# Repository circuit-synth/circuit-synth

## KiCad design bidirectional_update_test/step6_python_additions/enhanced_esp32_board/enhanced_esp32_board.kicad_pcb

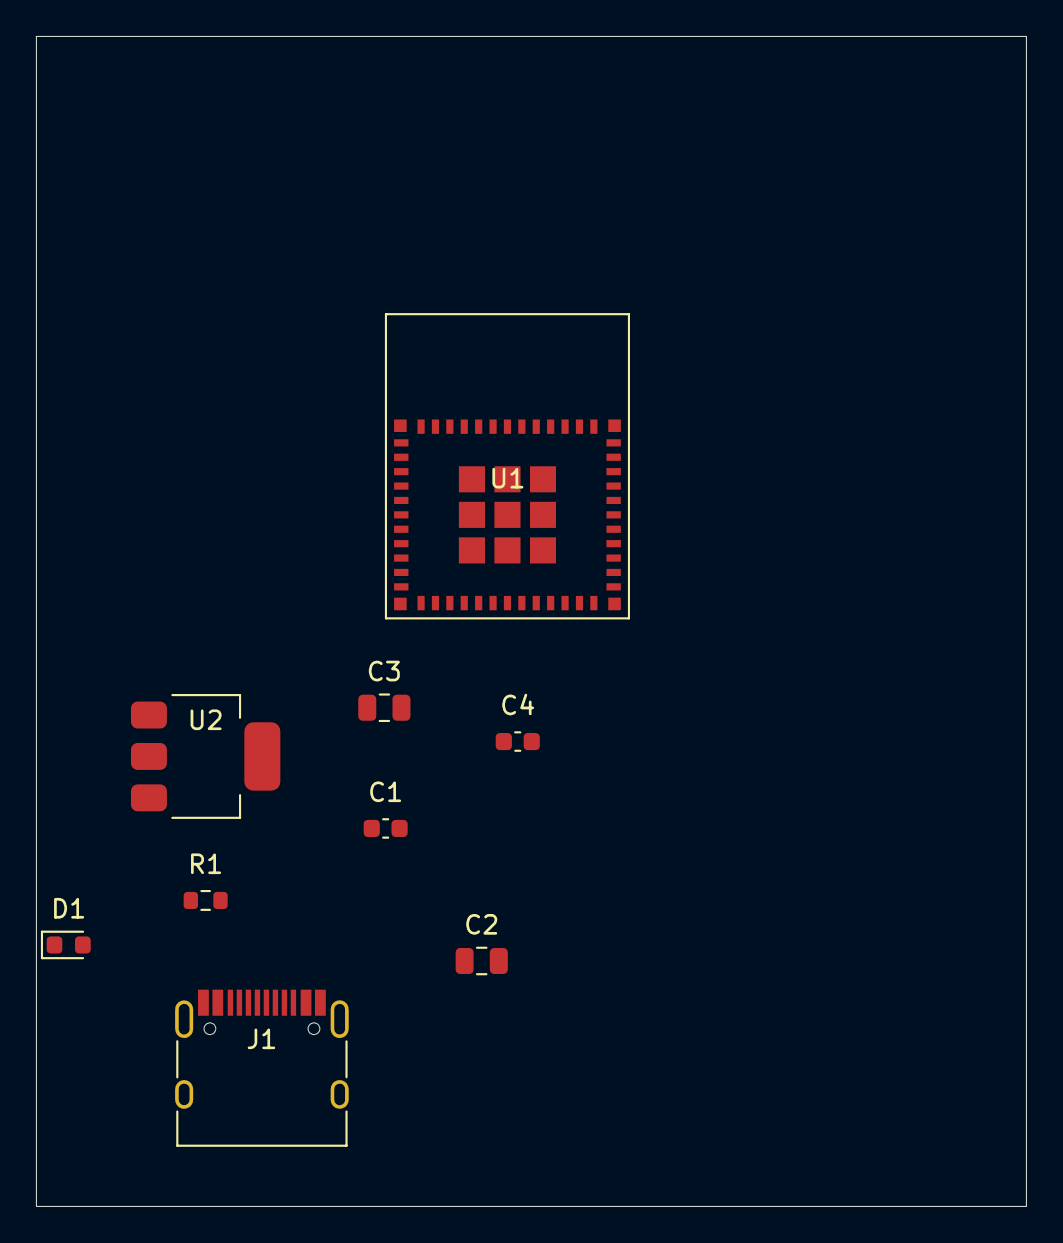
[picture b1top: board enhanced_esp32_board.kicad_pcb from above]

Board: 2 copper layers, 55.0 x 65.0 mm, 9 parts (0 on the bottom side), 4 nets, no tracks yet.

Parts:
C1: C; C_0603_1608Metric
C2: 10uF; C_0805_2012Metric
C3: 22uF; C_0805_2012Metric
C4: 100nF; C_0603_1608Metric
D1: Green LED; LED_0603_1608Metric
J1: USB-C; USB_C_Receptacle_HRO_TYPE-C-31-M-12
R1: 330R; R_0603_1608Metric
U1: ESP32-C6-MINI-1
U2: AMS1117-3.3; SOT-223-3_TabPin2

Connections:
+3V3: C1.1, C3.1, C4.1, R1.1, U1.3, U2.2
GND: C1.2, C2.2, C3.2, C4.2, D1.1, J1.A1, J1.A12, J1.B1, J1.B12, U1.1, U1.2, U1.11, U1.14, U1.36, U1.37, U1.38, U1.39, U1.40, U1.41, U1.42, U1.43, U1.44, U1.45, U1.46, U1.47, U1.48, U1.49, U1.50, U1.51, U1.52, U1.53, U2.1
LED_ANODE: D1.2, R1.2
VBUS_5V: C2.1, J1.A4, J1.A9, J1.B4, J1.B9, U2.3

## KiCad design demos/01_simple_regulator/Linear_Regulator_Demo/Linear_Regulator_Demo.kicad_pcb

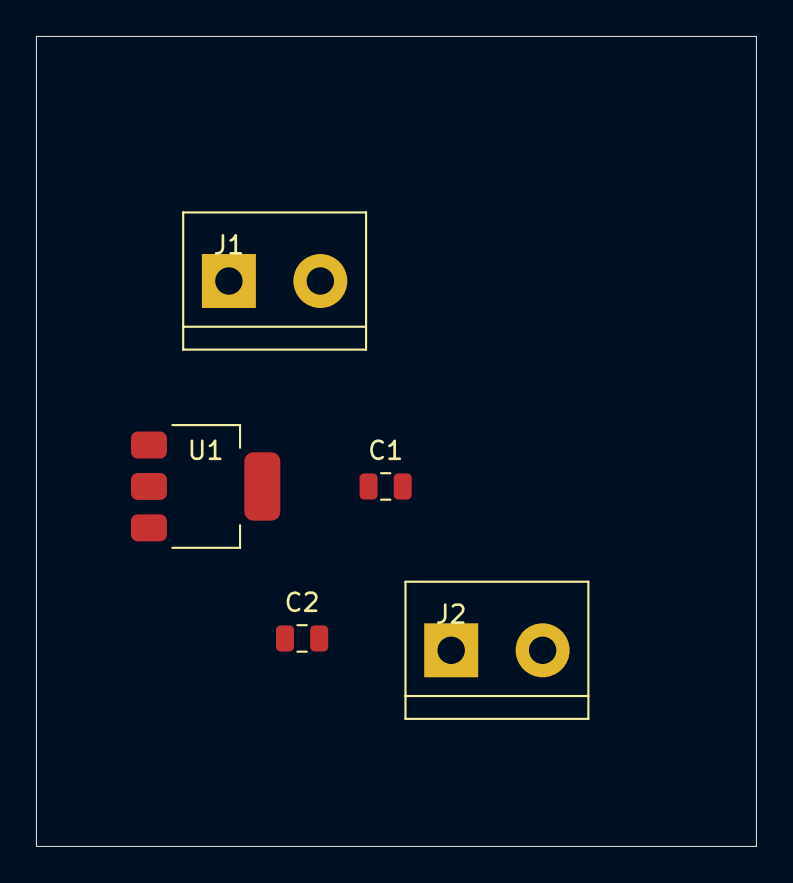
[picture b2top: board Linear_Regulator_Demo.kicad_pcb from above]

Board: 2 copper layers, 40.0 x 45.0 mm, 5 parts (0 on the bottom side), 3 nets, no tracks yet.

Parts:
C1: 10uF; C_0805_2012Metric
C2: 22uF; C_0805_2012Metric
J1, J2: TerminalBlock_bornier-2_P5.08mm
U1: SOT-223-3_TabPin2

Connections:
GND: C1.2, C2.2, J1.2, J2.2, U1.1
VIN_5V: C1.1, J1.1, U1.3
VOUT_3V3: C2.1, J2.1, U1.2

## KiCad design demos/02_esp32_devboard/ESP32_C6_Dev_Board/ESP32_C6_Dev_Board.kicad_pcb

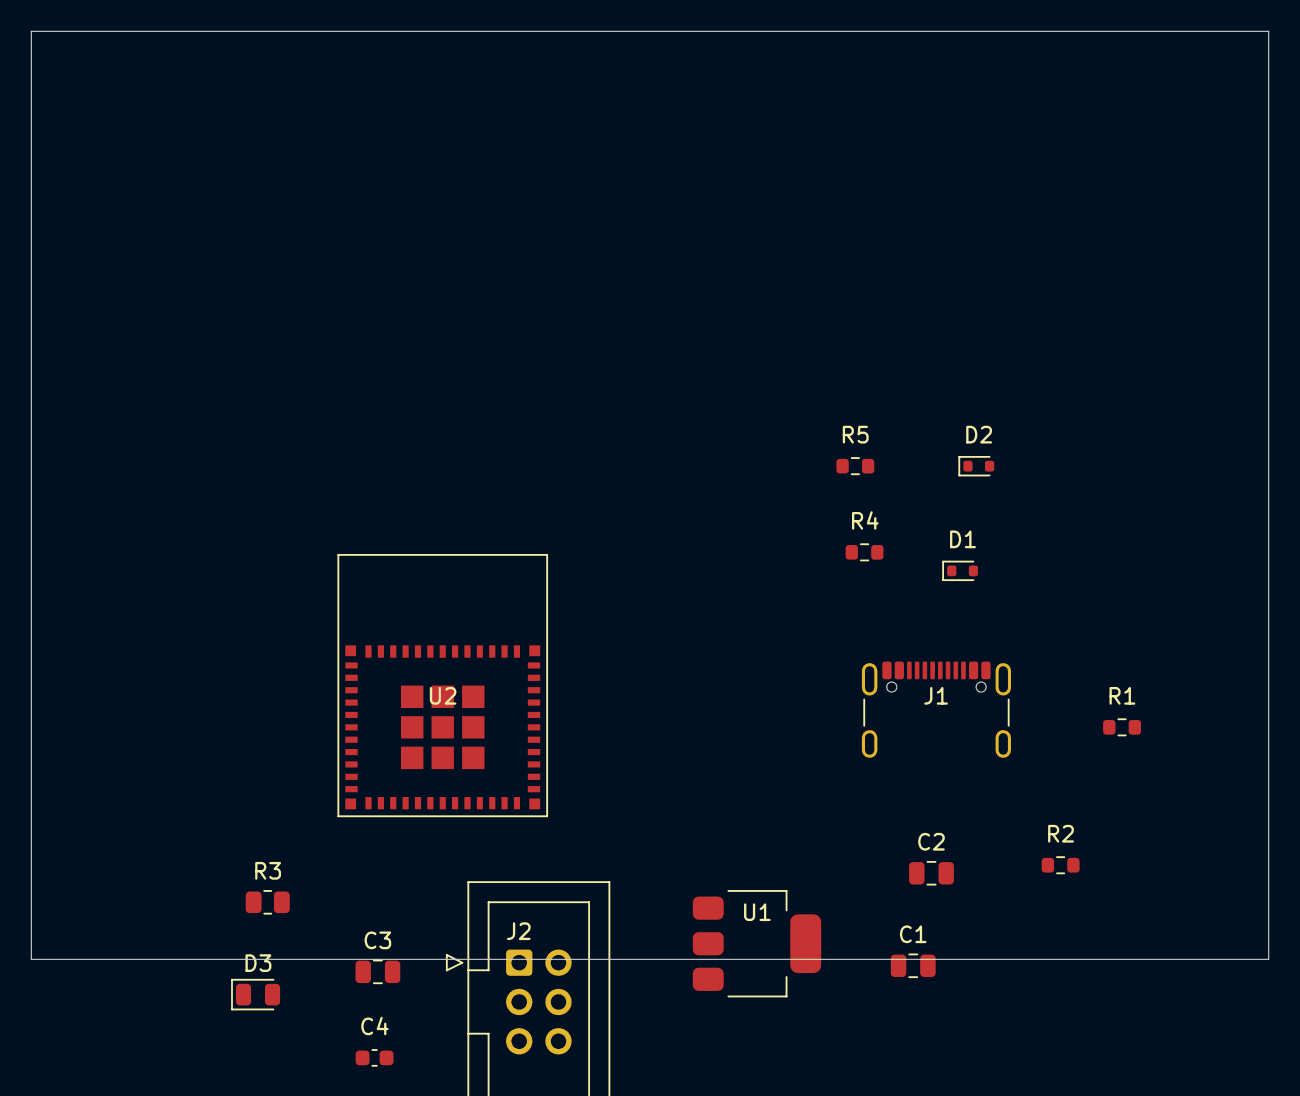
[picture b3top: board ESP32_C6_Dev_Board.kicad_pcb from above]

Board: 2 copper layers, 80.0 x 60.0 mm, 16 parts (0 on the bottom side), 15 nets, no tracks yet.

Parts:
C1, C2: 10uF; C_0805_2012Metric
C3: 22uF; C_0805_2012Metric
C4: 100nF; C_0603_1608Metric
D1, D2: D_SOD-523
D3: LED_0805_2012Metric
J1: USB_C_Receptacle_GCT_USB4105-xx-A_16P_TopMnt_Horizontal
J2: IDC-Header_2x03_P2.54mm_Vertical
R1, R2: 5.1k; R_0603_1608Metric
R3: 330; R_0805_2012Metric
R4, R5: 22; R_0603_1608Metric
U1: SOT-223-3_TabPin2
U2: ESP32-C6-MINI-1

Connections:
DEBUG_EN: J2.1, U2.8
DEBUG_IO0: J2.6, U2.12
DEBUG_RX: J2.5, U2.30
DEBUG_TX: J2.3, U2.31
GND: C1.2, C2.2, C3.2, C4.2, D1.2, D2.2, D3.1, J1.A1, J1.A12, J1.B1, J1.B12, J1.S1, J2.4, R1.2, R2.2, U1.1, U2.1, U2.2, U2.11, U2.14, U2.36, U2.37, U2.38, U2.39, U2.40, U2.41, U2.42, U2.43, U2.44, U2.45, U2.46, U2.47, U2.48, U2.49, U2.50, U2.51, U2.52, U2.53
LED_CONTROL: R3.1, U2.22
unnamed: J1.A5, R1.1
unnamed: J1.B5, R2.1
unnamed: D3.2, R3.2
USB_DM: D2.1, J1.A7, J1.B7, R5.1
USB_DM_MCU: R5.2, U2.25
USB_DP: D1.1, J1.A6, J1.B6, R4.1
USB_DP_MCU: R4.2, U2.24
VBUS: C1.1, C2.1, J1.A4, J1.A9, J1.B4, J1.B9, U1.3
VCC_3V3: C3.1, C4.1, J2.2, U1.2, U2.3
